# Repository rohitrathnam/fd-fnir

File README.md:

# Prototype Instrumentation for Frequency Domain fNIRS

## Abstract

Frequency domain fNIRS is a tissue optical measurement technique used to measure
absolute haemoglobin concentrations in brain tissue. This work is intended to
be the first step in the development of a wearable, low-cost FD-fNIRS device for
neurofeedback applications. The system requirements were generated from a review
of relevant literature. A simplified system architecture was developed based on the
various instrumentation methodologies proposed by various authors. The functional
blocks of this system were prototyped and their performance was evaluated. The
developed VCSEL current source was found to have a span of 10uA which meets the
design specifications. However, challenges exist in optimally biasing SiPM, which is
susceptible to optical and electronic noise sources.

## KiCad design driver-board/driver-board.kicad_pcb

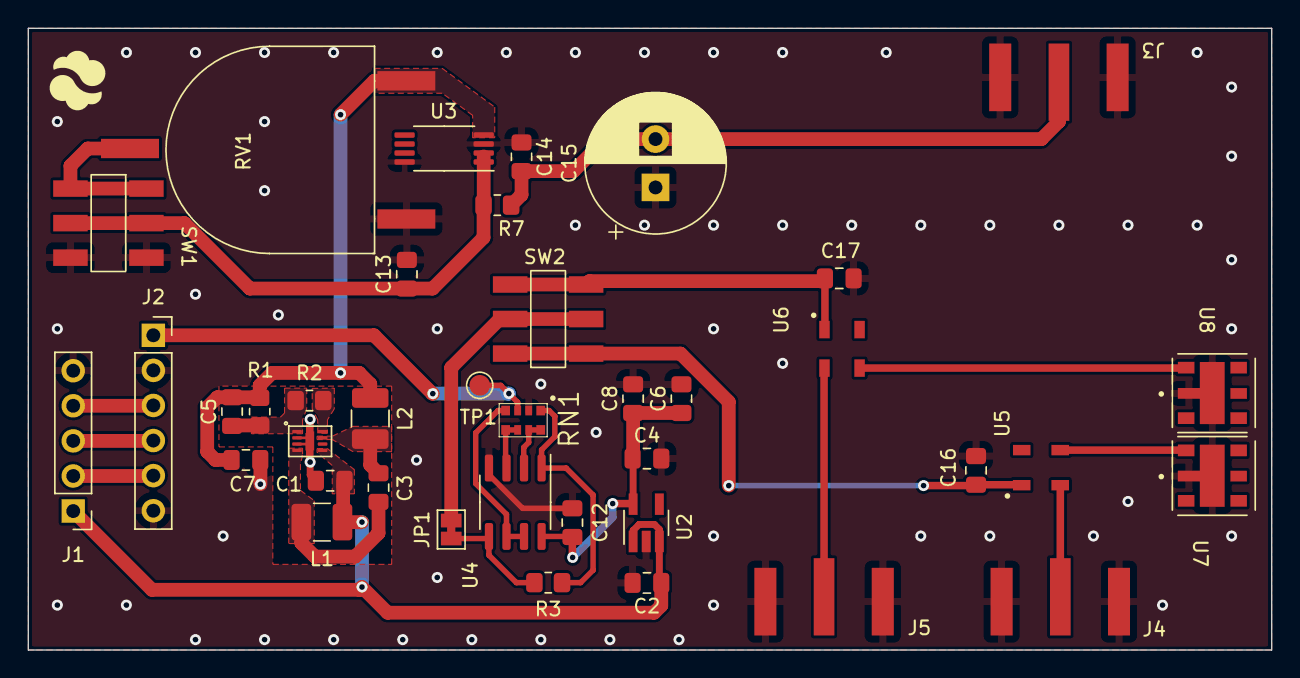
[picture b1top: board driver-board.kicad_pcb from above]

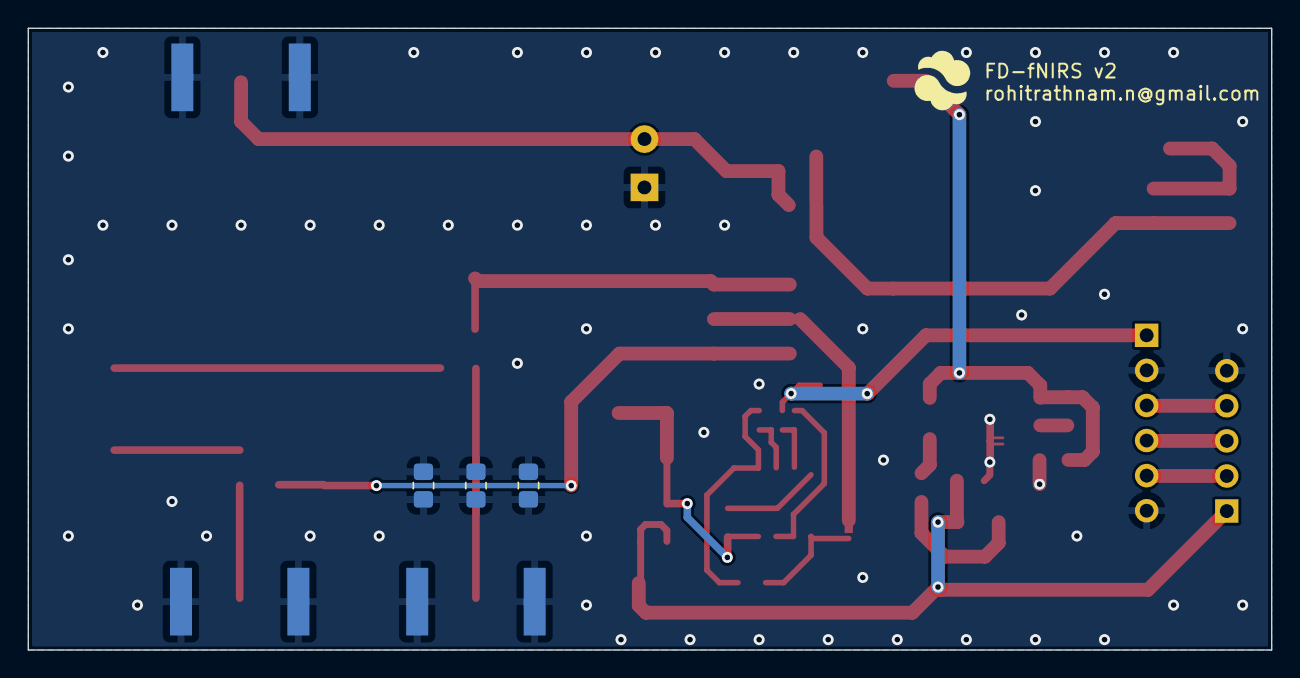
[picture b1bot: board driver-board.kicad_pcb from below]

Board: 2 copper layers, 90.0 x 45.0 mm, 44 parts (4 on the bottom side), 27 nets.

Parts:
C1, C2, C3, C4, C7: 1u; C_0805_2012Metric_Pad1.18x1.45mm_HandSolder
C5: 22p; C_0805_2012Metric_Pad1.18x1.45mm_HandSolder
C6, C8: 0; C_0805_2012Metric_Pad1.18x1.45mm_HandSolder
C12, C14: 0.1u; C_0805_2012Metric_Pad1.18x1.45mm_HandSolder
C13, C16, C17: 0.01u; C_0805_2012Metric_Pad1.18x1.45mm_HandSolder
C15: 100u; CP_Radial_D10.0mm_P3.50mm
FID1, FID1#2: Logo; mendi-logo-plain
J1: Conn_01x05_Male; PinHeader_1x05_P2.54mm_Vertical
J2: MCP4725; PinSocket_1x06_P2.54mm_Vertical
J3, J4, J5: Conn_Coaxial; CONSMA020.062-G
JP1: SolderJumper_2_Bridged; SolderJumper-2_P1.3mm_Bridged_Pad1.0x1.5mm
L1, L2: 22u; L_1210_3225Metric_Pad1.42x2.65mm_HandSolder
R1: 470k; R_0805_2012Metric_Pad1.20x1.40mm_HandSolder
R2: 18k; R_0805_2012Metric_Pad1.20x1.40mm_HandSolder
R3: 10; R_0805_2012Metric_Pad1.20x1.40mm_HandSolder
R4, R5, R6: 0; R_0805_2012Metric_Pad1.20x1.40mm_HandSolder
R7: 1k; R_0805_2012Metric_Pad1.20x1.40mm_HandSolder
RN1: R_Pack04_SIP_Split; ACASA5002S5002P1AT
RV1: 100K; PT15-RV15
SW1, SW2: BIAS ON/OF; JS202011SCQN
TP1: TestPoint; TestPoint_Pad_D1.5mm
U1: LT3462A
U2: MIC5317; SOT-23-5_HandSoldering
U3: LM2904; TSSOP-8_4.4x3mm_P0.65mm
U4: TSV358; SOIC-8-1EP_3.9x4.9mm_P1.27mm_EP2.29x3mm
U5, U6: TCBT-2R5G; TCBT
U7, U8: VCSEL; VP-SMD-5050

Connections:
3V3: J1.2, J2.5
5V: C1.2, C2.1, J1.1, L1.1, U1.5 (VIN), U2.1 (VIN), U2.3 (EN)
+3.3VA: C4.1, C6.1, C8.1, C12.1, U2.5 (VOUT), U4.8 (V+)
-33V: C5.2, C7.2, L2.2, R1.2, RV1.3, U3.4 (V-)
DAC_OUT_I_SRC: J2.1, RN1.3 (R3.1), TP1.1
DC_LD1: C16.2, SW2.1 (A), U5.1 (DC)
DC_LD2: C17.2, SW2.3 (C), U6.1 (DC)
GND: C1.1, C2.2, C4.2, C6.2, C7.1, C8.2, C12.2, C13.2, C14.1, C15.1, C16.1, C17.1, J1.5, J2.2, J2.6, J3.2 (Ext), J4.2 (Ext), J5.2 (Ext), R4.1, R4.2, R5.1, R5.2, R6.1, R6.2, RN1.2 (R2.1), RV1.1, SW1.3 (C), U1.2 (GND), U1.3 (GND), U1.9 (GND), U2.2 (GND), U3.3 (+), U3.8 (V+), U4.4 (V-), U7.1 (VCSEL-), U8.1 (VCSEL-)
unnamed: C3.1, L1.2, U1.4 (SW)
unnamed: C3.2, L2.1, U1.7 (D)
unnamed: C5.1, R1.1, R2.2, U1.1 (FB)
unnamed: C13.1, R7.2, SW1.2 (B), U3.1, U3.2 (-)
unnamed: J4.1 (In), U5.4 (RF)
unnamed: J5.1 (In), U6.4 (RF)
unnamed: JP1.1 (A), R3.1, U4.5 (+)
unnamed: JP1.2 (B), SW2.2 (B)
unnamed: R2.1, U1.8 (SDREF)
unnamed: R3.2, RN1.1 (R1.1), U4.1
unnamed: RN1.4 (R4.1), U4.6 (-), U4.7
unnamed: RN1.5 (R4.2), RN1.6 (R3.2), U4.3 (+)
unnamed: RN1.7 (R2.2), RN1.8 (R1.2), U4.2 (-)
unnamed: RV1.2, SW1.1 (A)
unnamed: U5.3 (RF+DC), U7.6 (VCSEL+)
unnamed: U6.3 (RF+DC), U8.6 (VCSEL+)
SCL0: J1.4, J2.3
SDA0: J1.3, J2.4
SiPM Bias: C14.2, C15.2, J3.1 (In), R7.1

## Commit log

2022-02-22 sim files
    added sim files, separate kicad project for driver and receiver, trans line calc for PCB
2022-02-24 Updated to low side driver
    modified schematic to low side driver, sim files for that, added footprints and 3D bodies for all components
2022-02-24 fix pot footprint
2022-02-25 more test points and design rules
2022-03-03 temp
2022-03-08 Anything
2022-03-08 pico modified sym/fp
2022-03-11 Passing DRC
2022-03-15 DRC passing, updated HV section and mounting
2022-03-16 Board reviewed, silk screen fixes
2022-03-16 changed design rules and via sizes for aisler
2022-04-13 added bom and pico code
2022-04-14 fixed RN1 fp
2022-04-14 fixed U2-EN pin
2022-04-14 fixed lt3462 fp, routing pending
2022-04-14 updated rst button fp
2022-05-23 added sym / fp for RF switch
2022-05-24 Cleanup, trying simpler board with no RF switch
2022-05-25 DRC passing
2022-05-27 minor fixes
2022-06-07 generated gerbers
2022-07-29 fw changes
2022-08-25 added report pdf
